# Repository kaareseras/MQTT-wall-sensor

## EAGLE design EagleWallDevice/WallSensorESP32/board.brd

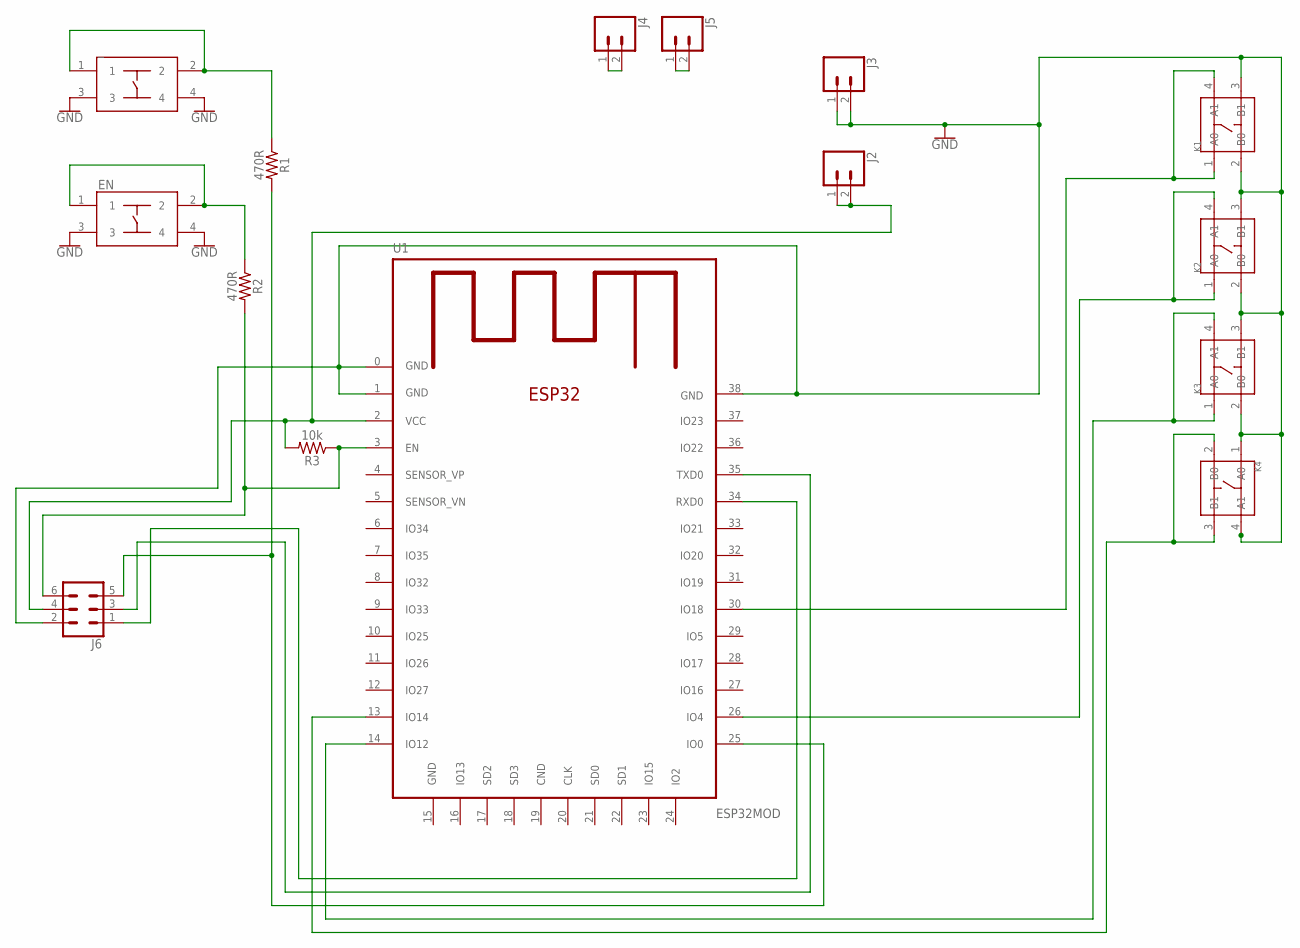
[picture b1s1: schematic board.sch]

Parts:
EN: TACTILE_SWITCH_DEV; TACTEIL_SWITCH_PAC
J2, J3, J4, J5: CONN_02; 1X02
J6: CONN_03X2FEMALE_SMD; 2X3_SMD
K1, K2, K3, K4: SMD-SWITCH-TACTILE-SPST-NO(4P-D6.0MM); SW4-SMD-6.0X6.0X5.0MM
R1, R2: 470R; 0603
R3: 10k; 0603
U1: ESP32MOD
_: TACTILE_SWITCH_DEV; TACTEIL_SWITCH_PAC

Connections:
GND: EN.3, EN.4, J3.1, J3.2, J6.2, K1.2 (B0), K1.3 (B1), K2.2 (B0), K2.3 (B1), K3.2 (B0), K3.3 (B1), K4.1 (A0), K4.4 (A1), U1.0 (GND), U1.1 (GND), U1.15 (GND), U1.38 (GND), _.3, _.4
unnamed: R1.1, _.1, _.2
unnamed: J6.6, R2.2, R3.1, U1.3 (EN)
unnamed: J2.1, J2.2, J6.4, R3.2, U1.2 (VCC)
unnamed: EN.1, EN.2, R2.1
unnamed: J4.1, J4.2
unnamed: J6.5, R1.2, U1.25 (IO0)
unnamed: K2.1 (A0), K2.4 (A1), U1.26 (IO4)
unnamed: K3.1 (A0), K3.4 (A1), U1.14 (IO12)
unnamed: K4.2 (B0), K4.3 (B1), U1.13 (IO14)
unnamed: J5.1, J5.2
unnamed: K1.1 (A0), K1.4 (A1), U1.30 (IO18)
unnamed: J6.3, U1.35 (TXD0)
unnamed: J6.1, U1.34 (RXD0)

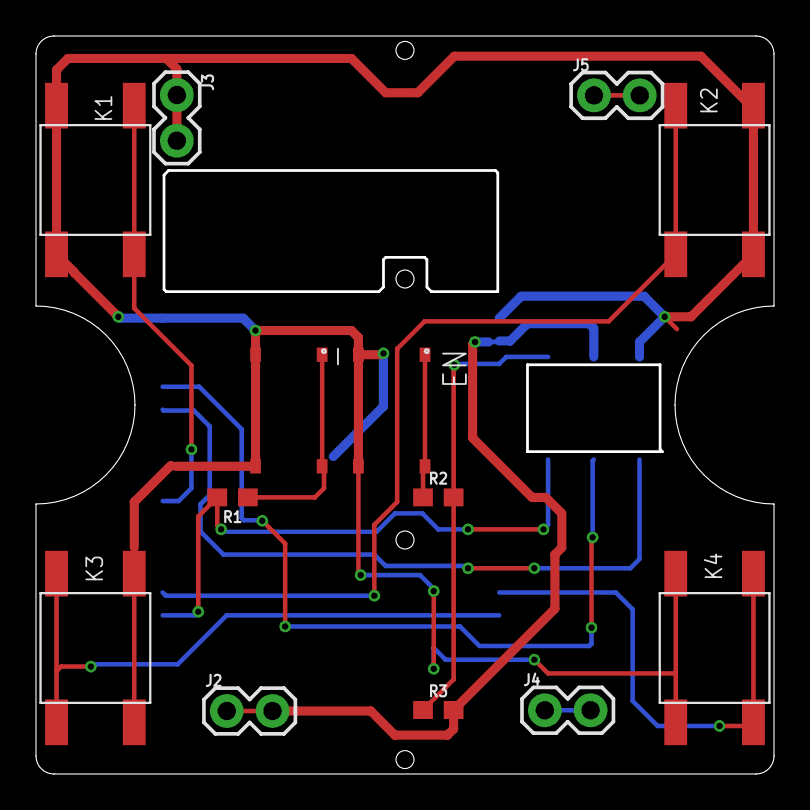
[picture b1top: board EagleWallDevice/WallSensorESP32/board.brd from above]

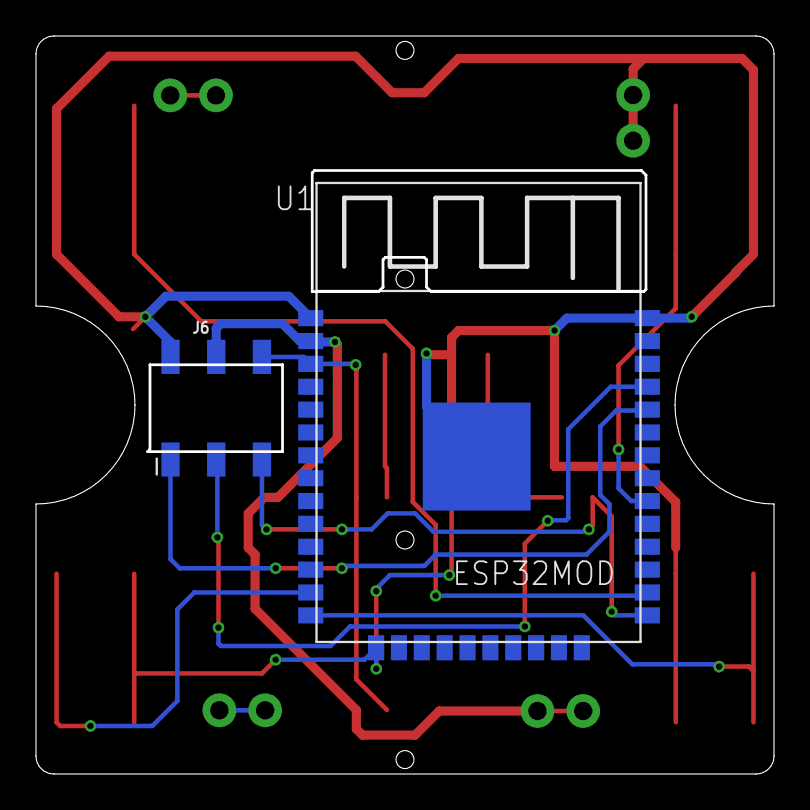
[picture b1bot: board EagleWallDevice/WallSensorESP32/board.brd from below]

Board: 2 copper layers, 40.8 x 40.8 mm, 15 parts (2 on the bottom side), 14 nets.

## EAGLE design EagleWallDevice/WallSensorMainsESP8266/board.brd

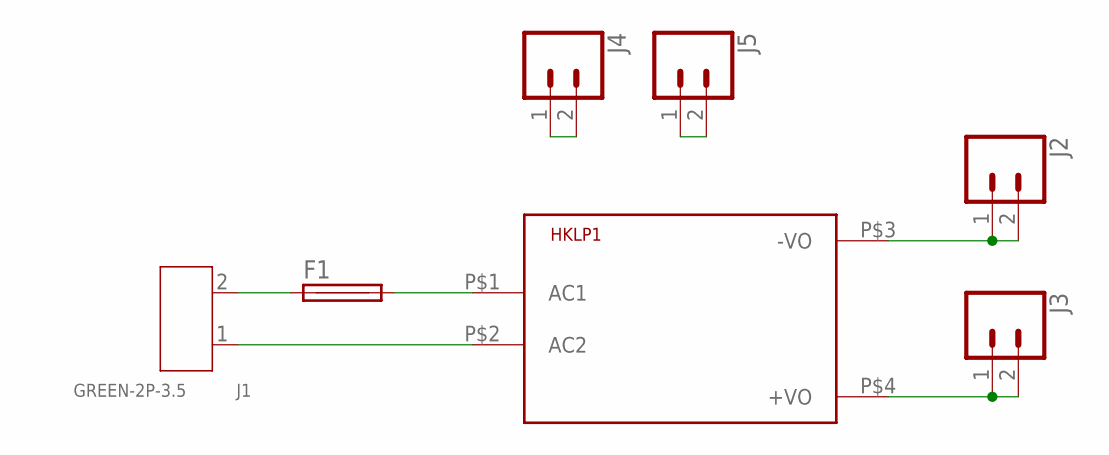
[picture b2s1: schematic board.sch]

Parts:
F1: TR5
HKLP1: HKLPM01
J1: GREEN-2P-3.5; H2-3.5-7.0X7.0MM
J2, J3, J4, J5: CONN_02; 1X02

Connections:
unnamed: F1.1, J1.2
unnamed: F1.2, HKLP1.P$1 (AC1)
unnamed: HKLP1.P$2 (AC2), J1.1
unnamed: HKLP1.P$4 (+VO), J3.1, J3.2
unnamed: J4.1, J4.2
unnamed: HKLP1.P$3 (-VO), J2.1, J2.2
unnamed: J5.1, J5.2

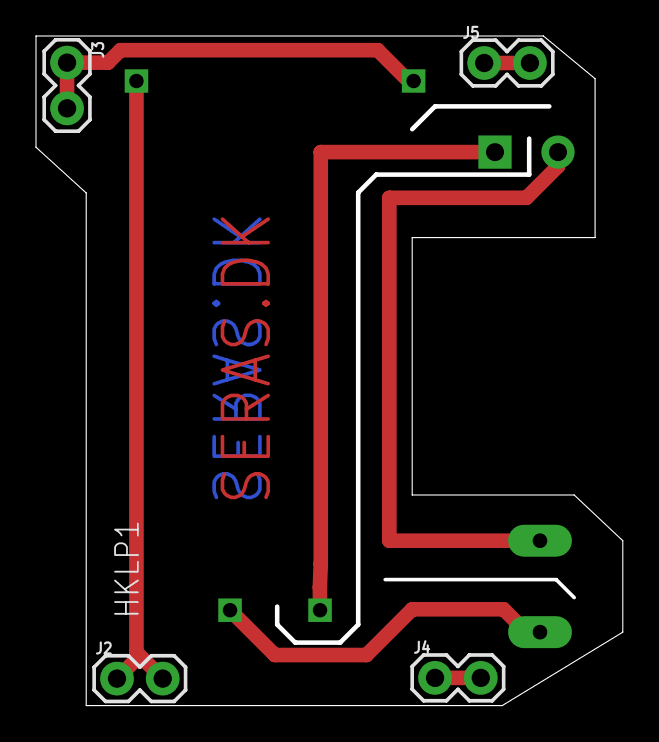
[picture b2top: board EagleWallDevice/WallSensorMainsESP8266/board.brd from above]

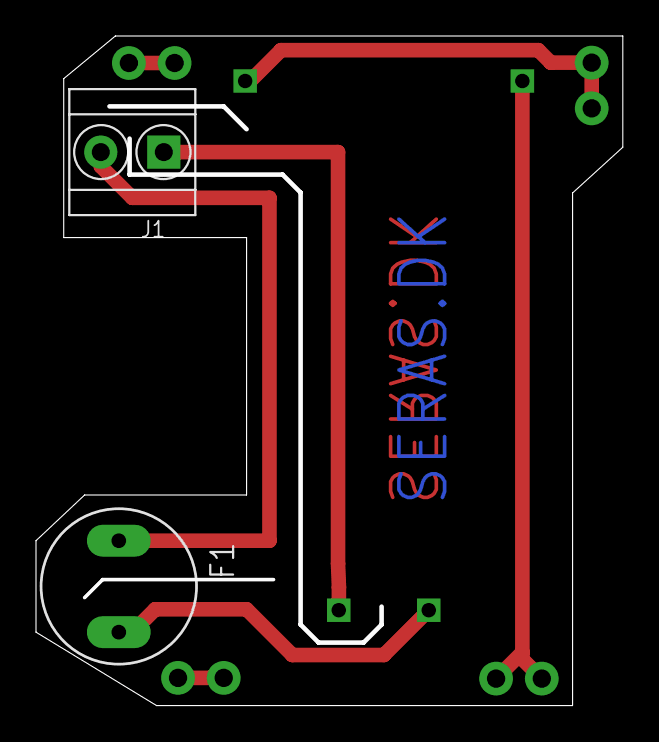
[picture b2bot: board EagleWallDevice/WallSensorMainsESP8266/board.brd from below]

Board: 2 copper layers, 32.3 x 36.9 mm, 7 parts (2 on the bottom side), 7 nets.

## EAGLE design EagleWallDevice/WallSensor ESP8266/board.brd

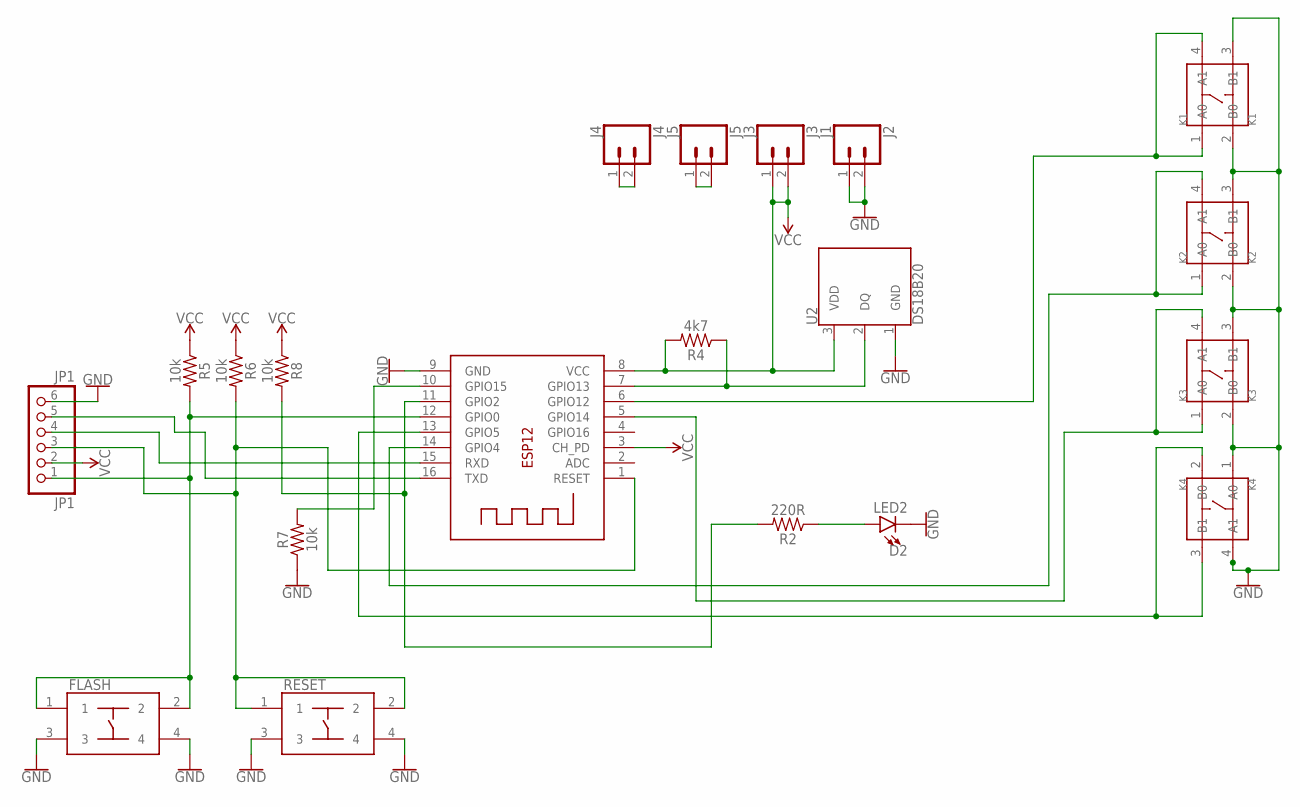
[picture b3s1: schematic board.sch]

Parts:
D2: LED2; LED_3MM
ESP: ESP; ESP-12
FLASH: TACTILE_SWITCH_DEV; TACTEIL_SWITCH_PAC
J2: J1; 1X02
J3: J3; 1X02
J4: J4; 1X02
J5: J5; 1X02
JP1: JP1; 1X06
K1: K1; SW4-SMD-6.0X6.0X5.0MM
K2: K2; SW4-SMD-6.0X6.0X5.0MM
K3: K3; SW4-SMD-6.0X6.0X5.0MM
K4: K4; SW4-SMD-6.0X6.0X5.0MM
R2: 220R; 0603
R4: 4k7; 0603
R5, R6, R7, R8: 10k; 0603
RESET: TACTILE_SWITCH_DEV; TACTEIL_SWITCH_PAC
U2: DS18B20; TO-92-AMMO

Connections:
GND: D2.K (C), ESP.9 (GND), FLASH.3, FLASH.4, J2.1, J2.2, JP1.6, K1.2 (B0), K1.3 (B1), K2.2 (B0), K2.3 (B1), K3.2 (B0), K3.3 (B1), K4.1 (A0), K4.4 (A1), R7.1, RESET.3, RESET.4, U2.1 (GND)
unnamed: ESP.10 (GPIO15), R7.2
unnamed: D2.A, R2.1
unnamed: ESP.16 (TXD), JP1.5
unnamed: ESP.13 (GPIO5), K4.2 (B0), K4.3 (B1)
unnamed: ESP.6 (GPIO12), K1.1 (A0), K1.4 (A1)
unnamed: ESP.15 (RXD), JP1.4
unnamed: J4.1, J4.2
unnamed: ESP.12 (GPIO0), FLASH.1, FLASH.2, JP1.1, R5.2
unnamed: ESP.14 (GPIO4), K2.1 (A0), K2.4 (A1)
unnamed: ESP.5 (GPIO14), K3.1 (A0), K3.4 (A1)
unnamed: J5.1, J5.2
unnamed: ESP.1 (RESET), JP1.3, R6.2, RESET.1, RESET.2
unnamed: ESP.7 (GPIO13), R4.1, U2.2 (DQ)
unnamed: ESP.11 (GPIO2), R2.2, R8.2
VCC: ESP.3 (CH_PD), ESP.8 (VCC), J3.1, J3.2, JP1.2, R4.2, R5.1, R6.1, R8.1, U2.3 (VDD)

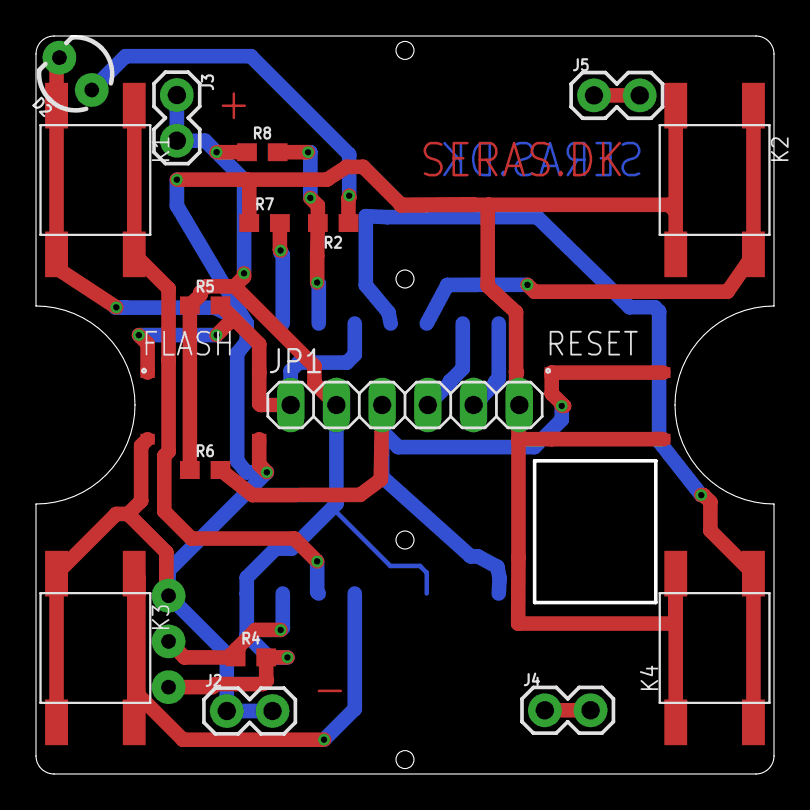
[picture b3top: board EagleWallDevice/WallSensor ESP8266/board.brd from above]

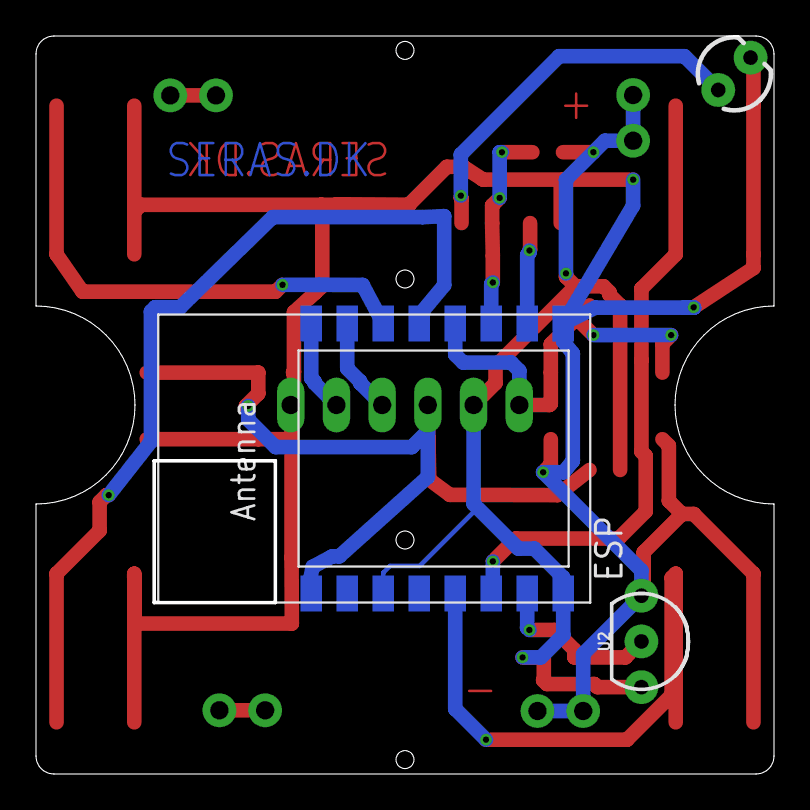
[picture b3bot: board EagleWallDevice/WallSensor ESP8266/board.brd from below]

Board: 2 copper layers, 40.8 x 40.8 mm, 20 parts (2 on the bottom side), 16 nets.

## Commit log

2021-10-31 added_project_files

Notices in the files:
parts and their libraries:
SparkFun-Connectors: Licensing: Creative Commons ShareAlike 4.0 International - https://creativecommons.org/licenses/by-sa/4.0
